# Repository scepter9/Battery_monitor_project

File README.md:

# BattSense: Smart Battery Health Monitoring System

## Introduction

BattSense is an STM32-based battery monitoring system designed to measure and monitor important battery parameters, including voltage, current, and temperature.

The motivation behind this project was to develop a practical embedded system that could collect battery measurements and provide useful information about its operating condition. Rather than relying on ready-made development boards and monitoring modules, I wanted to design a custom PCB and understand how the different hardware components work together.

The project combines microcontroller programming, sensor interfacing, analogue signal measurement, power management, and custom PCB design. It was developed using KiCad, with the STM32F103C8 serving as the main processing unit.

## Design

### Why BattSense?

Batteries are used in several applications, from portable electronics to renewable energy systems and electric vehicles. Monitoring their operating parameters is important for understanding their condition and identifying potentially unsafe operating conditions.

I chose to build BattSense to explore how an embedded system can monitor these parameters through external sensing circuits and process the collected data using a microcontroller.

The project also provides an opportunity to gain practical experience in custom PCB design, component selection, sensor interfacing, and developing hardware around an STM32 microcontroller.

### System Overview

The system is built around three primary measurements:

- **Voltage**: Measures the battery’s terminal voltage.
- **Current**: Measures the current flowing through an external test load.
- **Temperature**: Monitors battery temperature using an external NTC thermistor.

The STM32 processes the sensor readings and makes the measurement data available for display.

### Microcontroller: STM32F103C8

The STM32F103C8 was selected as the main controller because of its processing capability and range of integrated peripherals.

It is based on the ARM Cortex-M3 architecture and supports features such as:

- 12-bit ADC for analogue measurements
- GPIO for interfacing with external components
- I²C for communication with compatible peripherals
- SPI and USART communication interfaces
- SWD for programming and debugging

The ADC is particularly important to this project because it allows the microcontroller to read analogue signals from the voltage measurement circuit and temperature sensor.

### Voltage Measurement

Battery voltage is measured using a resistive voltage divider.

The divider consists of two resistors connected in series across the battery terminals. It scales the battery voltage down to a level suitable for the STM32’s ADC input.

This is necessary because the STM32 operates at 3.3 V logic levels, and its ADC input must remain within the permitted voltage range.

The microcontroller reads the divided voltage and calculates the original battery voltage using the voltage divider ratio.

### Current Measurement

Current measurement is implemented using an INA219 current-sensing IC and an external shunt resistor.

The INA219 measures the small voltage difference across the shunt resistor. Using the resistance value of the shunt, the current flowing through the circuit can be calculated.

The shunt resistor connects to the PCB through a dedicated two-pin connector, which carries the differential sensing signals to the INA219.

An RC filter network is incorporated into the sensing path to help reduce unwanted high-frequency noise. Additionally, two TVS diodes are included at the shunt connector to provide protection against transient voltage disturbances.

For this project, the battery supplies an external test load, with the current flowing through the shunt resistor. This allows the system to monitor the current drawn during battery testing.

### Temperature Measurement

Battery temperature is measured using an external 10 kΩ NTC thermistor.

Instead of mounting the thermistor directly on the PCB, a dedicated two-pin connector is provided for connecting the external temperature sensor.

The thermistor works with a fixed resistor to form a voltage divider. Since an NTC thermistor decreases in resistance as temperature increases, the voltage across the divider changes with temperature.

This analogue voltage is read by the STM32 ADC, and the microcontroller uses the thermistor’s characteristics to estimate the temperature.

The connector arrangement allows the temperature sensor to be positioned closer to the battery being monitored.

### External LCD Display

The system will use an external LCD to display the battery measurements.

Rather than integrating the LCD directly onto the main PCB, it will be soldered separately and connected to the STM32 through jumper wires.

This arrangement keeps the main PCB design separate from the display module while allowing the microcontroller to communicate with the LCD and present the measured battery parameters.

### Power Supply

The PCB includes power regulation circuitry to provide the required operating voltages for the microcontroller and other electronic components.

The power section is designed to provide stable supply voltages while supporting the different components used throughout the system.

### PCB Layout

The PCB was designed in KiCad, with the components arranged according to their functions and electrical connections.

The layout brings together the microcontroller, voltage measurement circuit, current-sensing circuit, temperature measurement circuit, and power supply section.

The current-sensing connector includes an RC filter network and TVS protection components. A separate two-pin connector is provided for the external NTC thermistor.

Care was taken during component placement and routing to organise the different sections of the design and provide clear connections between the sensing circuits and the STM32.

The schematic and PCB layout are included in the project repository to make the hardware design available for inspection and further development.

## Hardware Components

The major components used in the design include:

| Component                  | Purpose                                      |
|----------------------------|----------------------------------------------|
| STM32F103C8                | Main microcontroller                         |
| INA219                     | Current measurement                          |
| External shunt resistor    | Current sensing                              |
| RC filter network          | Filtering noise in the current-sensing path  |
| Two TVS diodes             | Transient protection at the shunt connector  |
| 47 kΩ and 10 kΩ resistors  | Voltage divider                              |
| 10 kΩ NTC thermistor       | External temperature measurement             |
| Fixed resistor             | Thermistor voltage divider                   |
| Two-pin connector          | External thermistor connection               |
| Two-pin connector          | Shunt sensing connection                     |
| Voltage regulators         | Power supply regulation                      |
| External LCD               | Displaying measurement readings              |
| Jumper wires               | Connecting the external LCD to the STM32     |

## How the System Works

The operation of BattSense can be summarised in the following stages:

1. **Voltage sensing**: The voltage divider scales down the battery voltage to a suitable level for the STM32 ADC.
2. **Current sensing**: The INA219 measures the voltage across the external shunt resistor to determine the current flowing through the test load.
3. **Signal conditioning and protection**: The RC filter network helps reduce noise in the current-sensing path, while the TVS diodes provide transient protection at the shunt connector.
4. **Temperature sensing**: The external NTC thermistor produces a temperature-dependent analogue voltage.
5. **Data processing**: The STM32 receives the sensor readings and processes them to obtain the corresponding voltage, current, and temperature values.
6. **Display**: The processed measurements are sent to the external LCD for presentation.

## Assembly and Documentation

The project was designed using KiCad. The repository contains the relevant hardware design files and supporting documentation.

The main design files include:

- KiCad schematic file
- KiCad PCB layout file
- KiCad project file
- Schematic PDF
- Bill of Materials (BOM) in CSV format
- PCB layout and 3D render images

These files make it possible to inspect the circuit, review component selections, modify the PCB, and continue development of the project.

## Lessons Learned

Working on BattSense provided practical experience in several areas of electronics and embedded systems.

Some of the key areas explored during the project include:

1. **STM32 Hardware Design**: Understanding the connections and supporting circuitry required when designing around an STM32 microcontroller.
2. **Analogue Measurements**: Using voltage dividers and ADC inputs to measure external electrical signals.
3. **Current Sensing**: Understanding how a shunt resistor and current-sensing IC work together.
4. **Signal Conditioning**: Incorporating RC filtering and TVS protection into external sensing connections.
5. **Sensor Interfacing**: Designing external sensor connections and reading temperature measurements using a microcontroller.
6. **PCB Design**: Translating a circuit schematic into a physical PCB layout using KiCad.

## Next Steps

The project provides a foundation for further development. Planned improvements include:

1. **Firmware Development**: Implementing the STM32 firmware for acquiring, processing, and displaying battery measurements.
2. **LCD Integration**: Connecting the external LCD using jumper wires and implementing the display interface.
3. **Calibration**: Comparing voltage, current, and temperature readings against appropriate reference instruments to evaluate measurement accuracy.
4. **Battery Testing**: Carrying out controlled battery tests and analysing the collected measurements.
5. **Further Improvements**: Exploring additional battery analysis features and improving the overall monitoring system.

## Project Files

The complete hardware design and supporting documentation are available in this repository.

- **KiCad Project**: `Hardware/KiCad/`
- **Schematic PDF**: `Hardware/Documentation/`
- **Bill of Materials**: `Hardware/Documentation/`
- **PCB Images**: `images/`
- **Fabrication Files**: `Hardware/Fabrication/`

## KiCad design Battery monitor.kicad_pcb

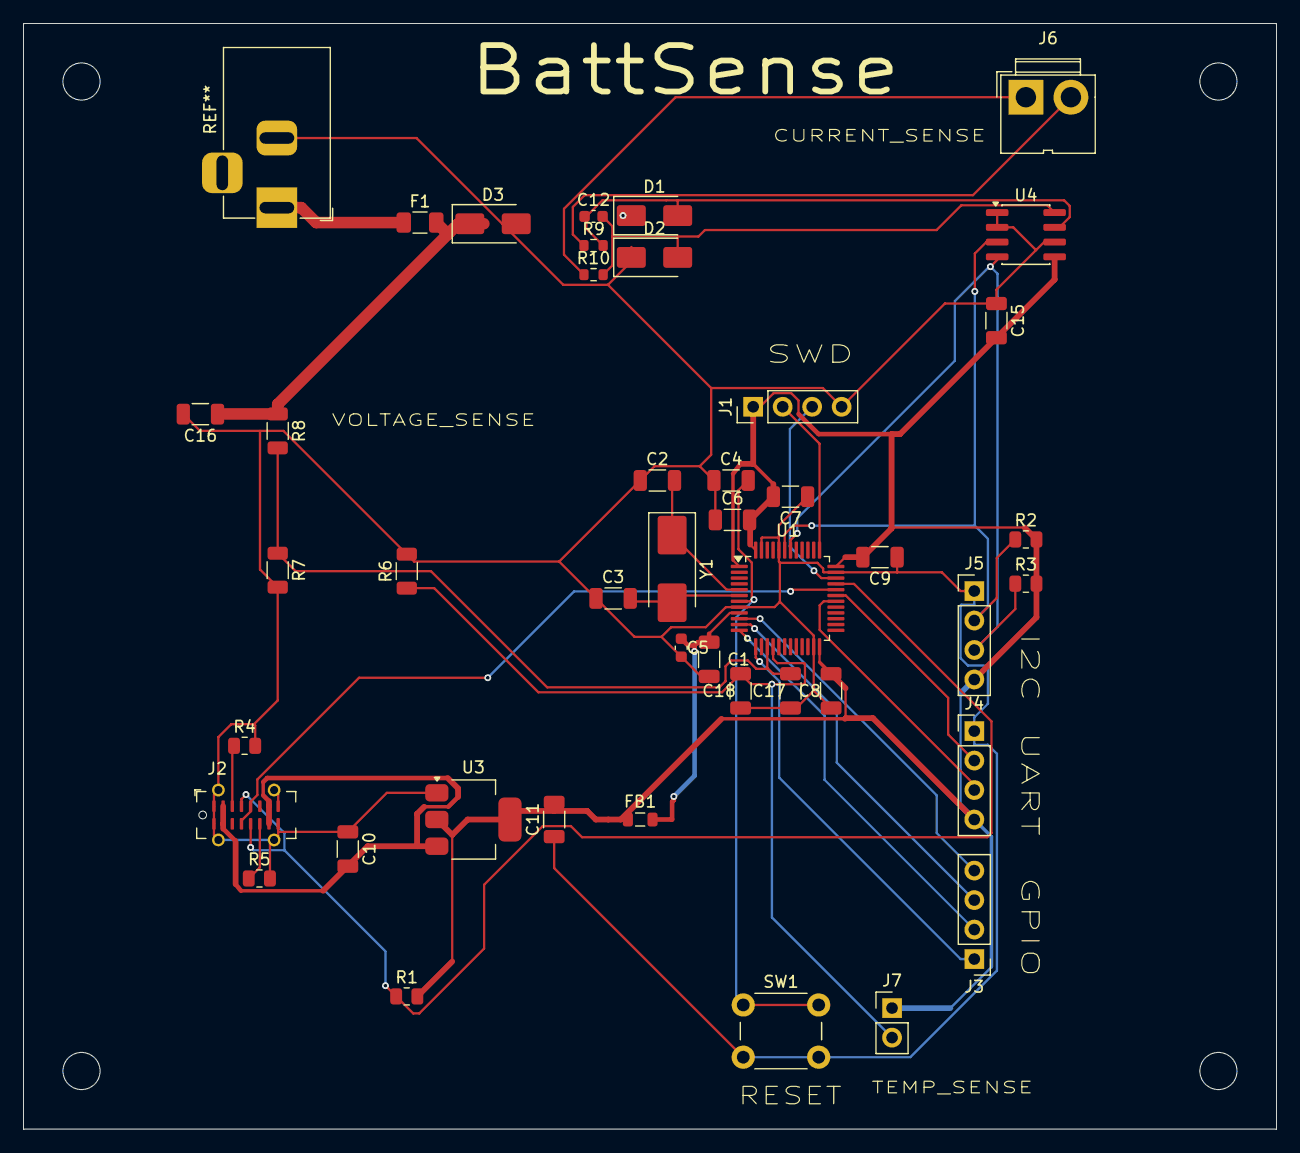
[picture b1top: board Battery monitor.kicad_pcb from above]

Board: 2 copper layers, 108.0 x 95.2 mm, 43 parts (0 on the bottom side), 28 nets.

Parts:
C1, C4, C6, C7, C8, C9, C15, C16, C17, C18: 100n; C_1206_3216Metric
C2, C3: 10p; C_1206_3216Metric
C5, C12: 0.1u; C_0603_1608Metric
C10: 10u; C_1206_3216Metric
C11: 22u; C_1206_3216Metric
D1, D2, D3: 17; D_SMA
F1: 2A; Fuse_1206_3216Metric
FB1: FerriteBead; L_0805_2012Metric
J1, J3, J4, J5: Conn_01x04_Pin; PinHeader_1x04_P2.54mm_Vertical
J2: USB_C_Receptacle_USB2.0_16P; USB_C_Receptacle_G-Switch_GT-USB-7051x
J6: Conn_01x02_Pin; JWT_A3963_1x02_P3.96mm_Vertical
J7: Conn_01x02_Pin; PinHeader_1x02_P2.54mm_Vertical
R1: 1.5k; R_0805_2012Metric
R2, R3: 4.7k; R_0805_2012Metric
R4, R5: 5.1k; R_0805_2012Metric
R6, R7: 10K; R_1206_3216Metric
R8: 47K; R_1206_3216Metric
R9, R10: 10; R_0603_1608Metric
SW1: SW_Push; SW_PUSH_6mm
U1: STM32F103C8Tx; LQFP-48_7x7mm_P0.5mm
U3: AMS1117-3.3; SOT-223-3_TabPin2
U4: INA219AxD; SOIC-8_3.9x4.9mm_P1.27mm
Y1: 16MHz; Crystal_SMD_0603-2Pin_6.0x3.5mm_HandSoldering

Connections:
3.3V: C6.2, C7.2, C8.2, C9.2, C11.2, C15.2, FB1.1, J1.1, J4.4, J5.4, J7.1, R1.2, R2.2, R3.2, U1.1 (VBAT), U1.24 (VDD), U1.36 (VDD), U1.48 (VDD), U3.2 (VO), U4.5 (VS)
3.3V_AN: C1.1, C5.1, FB1.2, U1.9 (VDDA)
CC1: J2.A5 (CC1), R4.1
CC2: J2.B5 (CC2), R5.1
GND: C1.2, C2.1, C3.1, C4.1, C5.2, C6.1, C7.1, C8.1, C9.1, C10.1, C11.1, C15.1, C16.2, C17.1, C18.1, D1.1 (A1), D2.1 (A1), D3.2 (A2), J1.4, J2.A1 (GND), J2.A12 (GND), J2.B1 (GND), J2.B12 (GND), J2.S1 (SHIELD), J4.1, J5.1, R4.2, R5.2, R6.2, R7.2, SW1.2, U1.8 (VSSA), U1.23 (VSS), U1.35 (VSS), U1.44 (BOOT0), U1.47 (VSS), U3.1 (GND), U4.1 (A1), U4.2 (A0), U4.6 (GND)
unnamed: C12.1, D1.2 (A2), R9.2, U4.7 (IN-)
unnamed: C12.2, D2.2 (A2), R10.2, U4.8 (IN+)
unnamed: J1.2, U1.37 (PA14)
unnamed: J1.3, U1.34 (PA13)
unnamed: J3.1, U1.13 (PA3)
unnamed: J3.2, U1.12 (PA2)
unnamed: J3.3, U1.11 (PA1)
unnamed: J3.4, U1.10 (PA0)
unnamed: J4.2, U1.31 (PA10)
unnamed: J4.3, U1.30 (PA9)
unnamed: J6.1, R10.1
unnamed: J6.2, R9.1
unnamed: C4.2, SW1.1, U1.7 (NRST)
unnamed: C2.2, U1.5 (PD0), Y1.1
unnamed: C3.2, U1.6 (PD1), Y1.2
unnamed: C10.2, J2.A4 (VBUS), J2.A9 (VBUS), J2.B4 (VBUS), J2.B9 (VBUS), U3.3 (VI)
PA5: C17.2, R7.1, R8.2, U1.15 (PA5)
PA6: C18.2, J7.2, R6.1, U1.16 (PA6)
PA11: J2.A7 (D-), J2.B7 (D-), U1.32 (PA11)
PA12: J2.A6 (D+), J2.B6 (D+), R1.1, U1.33 (PA12)
STM_PB6_SCL: J5.3, R3.1, U1.42 (PB6), U4.4 (SCL)
STM_PB7_SDA: J5.2, R2.1, U1.43 (PB7), U4.3 (SDA)
VOLT_SENSE_POWER: C16.1, D3.1 (A1), F1.2, R8.1
